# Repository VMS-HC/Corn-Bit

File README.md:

<div align='center'>

<h1>A lil 8-bit Dev board!</h1>
<p>A Attiny dual linked project!</p>

<h4> <a href=https://kicanvas.org/?repo=https%3A%2F%2Fgithub.com%2FVMS-HC%2FCorn-Bit%2Fblob%2Fmain%2FHardware%2FCorn-bit.kicad_sch>View Demo</a> <span> · </span> <a href="https://github.com/Bobert3D/Corn-Bit/blob/master/README.md"> Documentation </a> <span> · </span> <a href="https://github.com/Bobert3D/Corn-Bit/issues"> Report Bug </a> <span> · </span> <a href="https://github.com/Bobert3D/Corn-Bit/issues"> Request Feature </a> </h4>

</div>

# :notebook_with_decorative_cover: Table of Contents

- [About the Project](#star2-about-the-project)
- [Roadmap](#compass-roadmap)
- [FAQ](#grey_question-faq)
- [License](#warning-license)
- [Author](#handshake-author)
- [Acknowledgements](#gem-acknowledgements)

## :star2: About the Project

### :camera: Screenshots
<div align="center">  </div>
<div align="center">  </div>

### :dart: Features
- 2 Attiny412s!!
- I/O Expander!
- Simple programming!

### :art: Color Reference
| Color | Hex |
| --------------- | ---------------------------------------------------------------- |
| Primary Color |  #17cfb4 |
| Secondary Color |  #0e218b |
| Accent Color |  #11731b |
| Text Color |  #a40459 |

## :toolbox: Getting Started

### :bangbang: Prerequisites

- KICAD!!!<a href="kicad.org"> Here</a>
```bash
 xdg-open https:kicad.org
```

### :gear: Installation

Follow the KICAD install guide and then download the project's files (name.kicad_sch, name.kicad_pcb, name.kicad_pro)!
```bash
sudo add-apt-repository --yes ppa:kicad/kicad-10.0-releases sudo apt update sudo apt install --install-recommends kicad
```

### :running: Run Locally

Clone the project

```bash
https://github.com/VMS-HC/Corn-Bit
```
Duel Attiny412 dev/processing board!
```bash
cd ~/corn-bit
```

## :compass: Roadmap

* [x] Changed from 3 Attiny412's to 2!
* [ ] Add integrated display
* [ ] Add other UI interface or tools!
* [x] Finished V1.1!

## :wave: Contributing

Contributions are always welcome!

see `contributing.md` for ways to get started

### :scroll: Code of Conduct

Please read the [Code of Conduct](https://github.com/VMS-HC/Corn-Bit/blob/master/CODE_OF_CONDUCT.md)

## :grey_question: FAQ

- Is this a complex project?
- NOPE! If you can solder and know what kicad is(kinda lol). This is great for you!
- Can I contribute?
- YES please do! Check out the Contributions section! ty.
- Where can I learn stuff like this as a teenager? (13-18)!
- Hack Club! Go to Hackclub.com and take a peek and get some free stickers!

## :warning: License

Distributed under the MIT License. See LICENSE.txt for more information.

## :handshake: Author

Bobert3D!

Project Link: [https://github.com/VMS-HC/Corn-Bit](https://github.com/VMS-HC/Corn-Bit)

## :gem: Acknowledgements

- [Thanks to And at HC Slack and all the peeps who helped me keep this from becoming a bomb of electronics...](Take a peek at kicad docs!)

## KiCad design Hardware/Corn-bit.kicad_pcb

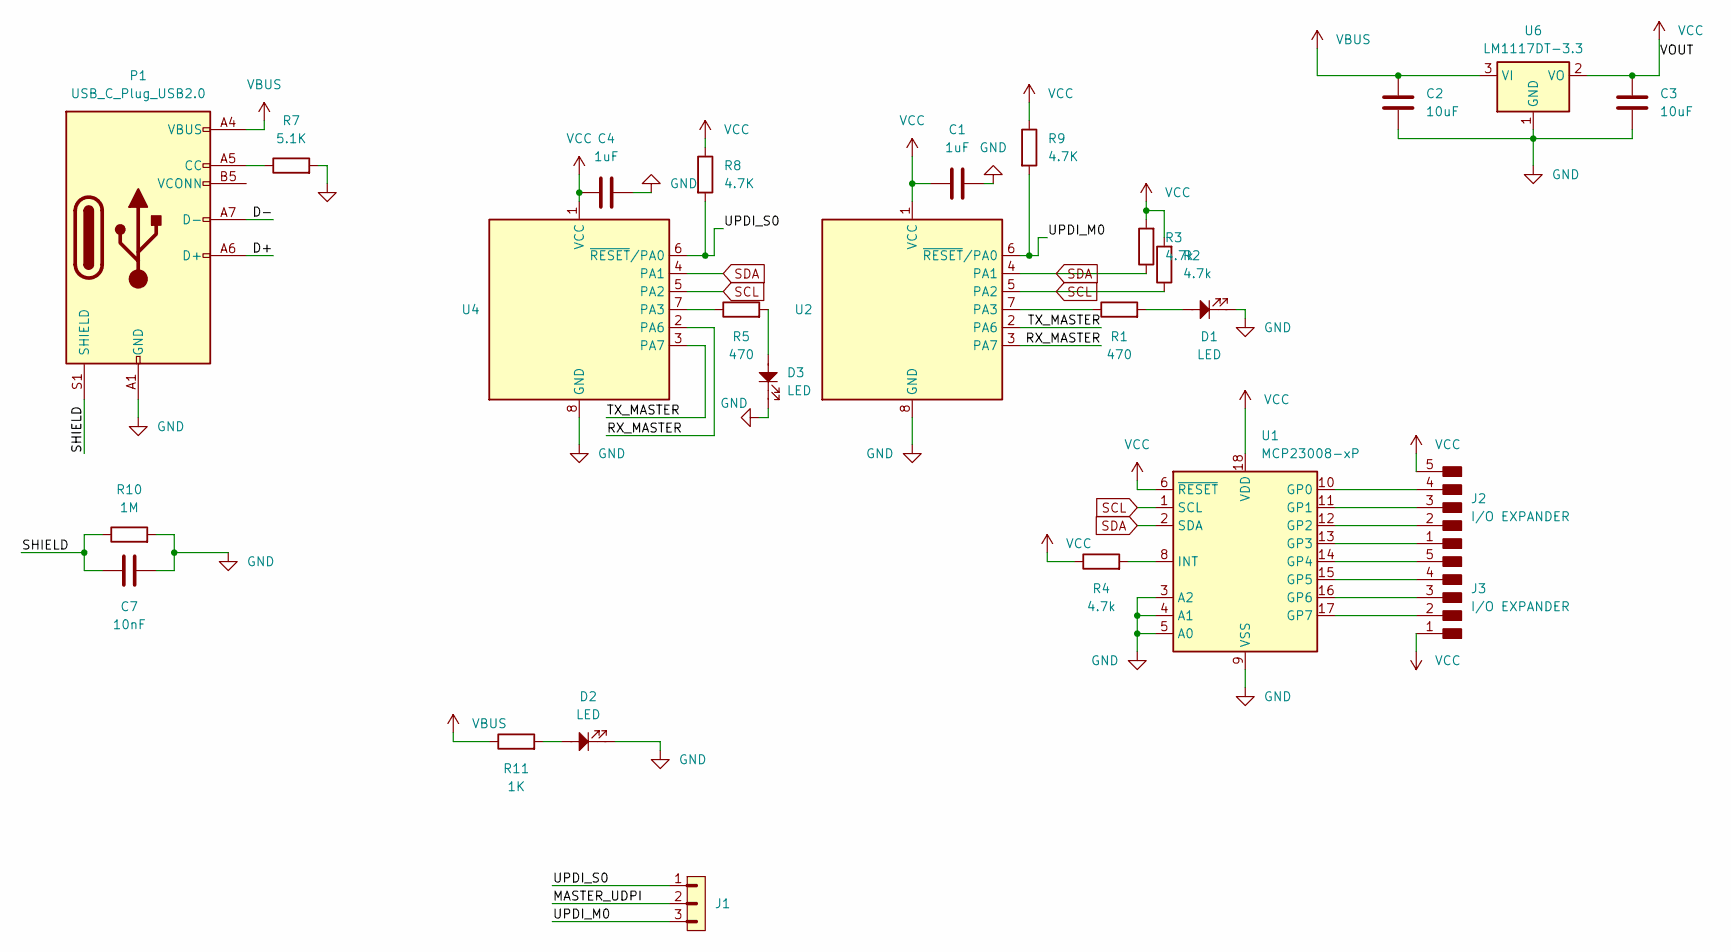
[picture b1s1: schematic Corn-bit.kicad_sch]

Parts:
C1, C4: 1uF; C_0805_2012Metric
C2, C3: 10uF; C_Disc_D5.0mm_W2.5mm_P2.50mm
C7: 10nF; C_0805_2012Metric
D1, D2, D3: LED; LED_0805_2012Metric
J1: PINHD_1x3_Male; PinHeader_1x03_P2.54mm_Vertical
J2, J3: I/O EXPANDER; PinHeader_01x05_P2.54mm_Vertical_THT_D1.4mm
P1: USB_C_Plug_USB2.0; USB_C_Receptacle_HRO_TYPE-C-31-M-12
R1, R5: 470; R_0805_2012Metric
R2, R3, R4: 4.7k; R_0805_2012Metric
R7: 5.1K; R_0805_2012Metric
R8, R9: 4.7K; R_0805_2012Metric
R10: 1M; R_0805_2012Metric
R11: 1K; R_0805_2012Metric
U1: MCP23008-xP; SMDIP-18_W7.62mm
U2, U4: ATtiny412-SS; SOIC-8-1EP_3.9x4.9mm_P1.27mm_EP2.29x3mm
U6: LM1117DT-3.3; TO-252-3_TabPin2

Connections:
/D+: P1.A6 (D+)
/D-: P1.A7 (D-)
/MASTER_UDPI: J1.2
/RX_MASTER: U2.3 (PA7), U4.2 (PA6)
/SHIELD: C7.2, P1.S1 (SHIELD), R10.1
/TX_MASTER: U2.2 (PA6), U4.3 (PA7)
/UPDI_M0: J1.3, R9.2, U2.6 (~RESET/PA0)
/UPDI_S0: J1.1, R8.2, U4.6 (~RESET/PA0)
GND: C1.2, C2.1, C3.1, C4.2, C7.1, D1.1, D2.1, D3.1, P1.A1 (GND), P1.A12 (GND), P1.B1 (GND), P1.B12 (GND), R7.2, R10.2, U1.3 (A2), U1.4 (A1), U1.5 (A0), U1.9 (VSS), U2.8 (GND), U4.8 (GND), U6.1 (GND)
unnamed: D1.2, R1.2
unnamed: D2.2, R11.2
unnamed: D3.2, R5.2
unnamed: J2.1, U1.13 (GP3)
unnamed: J2.2, U1.12 (GP2)
unnamed: J2.3, U1.11 (GP1)
unnamed: J2.4, U1.10 (GP0)
unnamed: J3.2, U1.17 (GP7)
unnamed: J3.3, U1.16 (GP6)
unnamed: J3.4, U1.15 (GP5)
unnamed: J3.5, U1.14 (GP4)
unnamed: P1.A5 (CC), R7.1
unnamed: R4.2, U1.8 (INT)
unnamed: R1.1, U2.7 (PA3)
unnamed: R5.1, U4.7 (PA3)
SCL: R2.1, U1.1 (SCL), U2.5 (PA2), U4.5 (PA2)
SDA: R3.1, U1.2 (SDA), U2.4 (PA1), U4.4 (PA1)
VBUS: C2.2, P1.A4 (VBUS), P1.A9 (VBUS), P1.B4 (VBUS), P1.B9 (VBUS), R11.1, U6.3 (VI)
VCC: C1.1, C3.2, C4.1, J2.5, J3.1, R2.2, R3.2, R4.1, R8.1, R9.1, U1.6 (~RESET), U1.18 (VDD), U2.1 (VCC), U4.1 (VCC), U6.2 (VO)

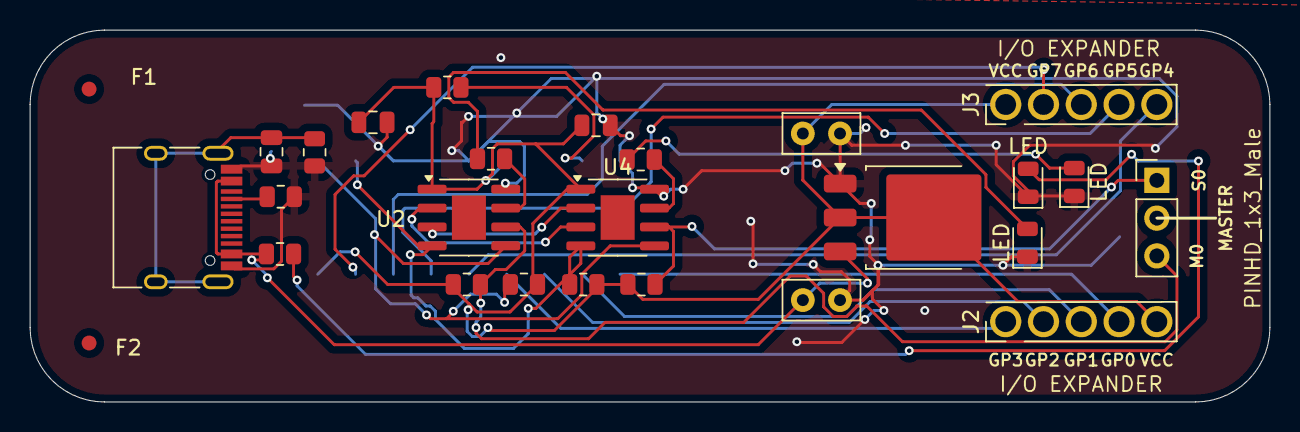
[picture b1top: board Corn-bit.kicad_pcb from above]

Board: 2 copper layers, 83.4 x 25.0 mm, 28 parts (1 on the bottom side), 25 nets.

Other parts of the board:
F1, F2: Fiducial_1mm_Mask3mm
